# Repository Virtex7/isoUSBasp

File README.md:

isoUSBasp
=========

3kV isolated USBasp-compatible Atmel AVR8 USB programmer

description in German Language:

3kV Dauerlast-isolierter USBasp mit Leistungstreibern am Ausgang

diese Version des bekannten Atmel-Programmiergeräts USBasp von Thomas Fischl
enthält ein paar zusätzliche Fähigkeiten:

- überall LEDs
- LEDs statt Zenerdioden am USB-Port (schöner!)
- galvanisch isolierter ISP-Port
- galvanisch getrennte Target-Supplyfunktion bis 200mA in 3,3 und 5V
- automatische Einstellung der Programmierspannung
- Leistungstreiber an den Programmierpins mit je +-70mA dauerkurzschlussfest
- Schmitt-Trigger-Eingänge mit Signalrückgewinnung
- per Schalter einstellbare slowSCK-Funktionalität für 128kHz-Targets

effektiv soll dieser Programmieradapter überall eingesetzt werden, auch wenn das Target
auf einer viel höheren Spannungsebene liegt, als der zur Programmierung eingesetzte PC.
Auch werden durch eine Massetrennung Masseschleifen und damit bedingte Fehlerströme
vermieden, die zur Beschädigung des PCs und des Programmiergeräts führen können.

Desweiteren ist jeder Programmierpin mit Schutzbeschaltung gegen Überspannung,
Dauerkurzschluss und in Grenzen gegen Rückspeisung geschützt.

Die Programmierspannung stellt sich automatisch ein, wenn am Vref-Pin des ISP-Anschlusses
eine Spannung anliegt. Default ist 3,3V, auch wenn keine Spannung am Vref-Pin liegt.
Umschaltgrenze ist 3,6V, dabei wird dann auf 5V ISP-Spannung umgeschaltet.

Es ist auch möglich den Vref-Anschluss zu bestromen, also das Target mit Strom zu
versorgen. Maximalstrom ist dabei 200mA bei 5V und ca 300mA bei 3,3V, durch einen
Widerstand dauerhaft kurzschlussfest. (dabei bricht die Spannung zusammen)

Hardware:

Schaltplan und Layout und alle nötigen Libs wurden entweder von mir erstellt oder sind
Teil des OpenSource-Projekts KiCad (EDA)
Ich empfehle die Verwendung einer selbst kompilierten Version von KiCad, da diese die
aktuellste Version ist und KiCad momentan recht schnell entwickelt wird.

Software:

Das Produkt ist zu fast 100% kompatibel zur FISCHL-USBasp-Software, dafür wurden ein paar
Inverter extra verbaut, das hätte man auch in Software machen können.
Allerdings muss das Relais an PC3 nach erfolgter Anmeldung am USB angeschaltet werden,
das ist und wird die einzige Modifikation an der Software.

Daher verweise ich auch auf die Homepage von Thomas Fischl:
http://www.fischl.de/usbasp/

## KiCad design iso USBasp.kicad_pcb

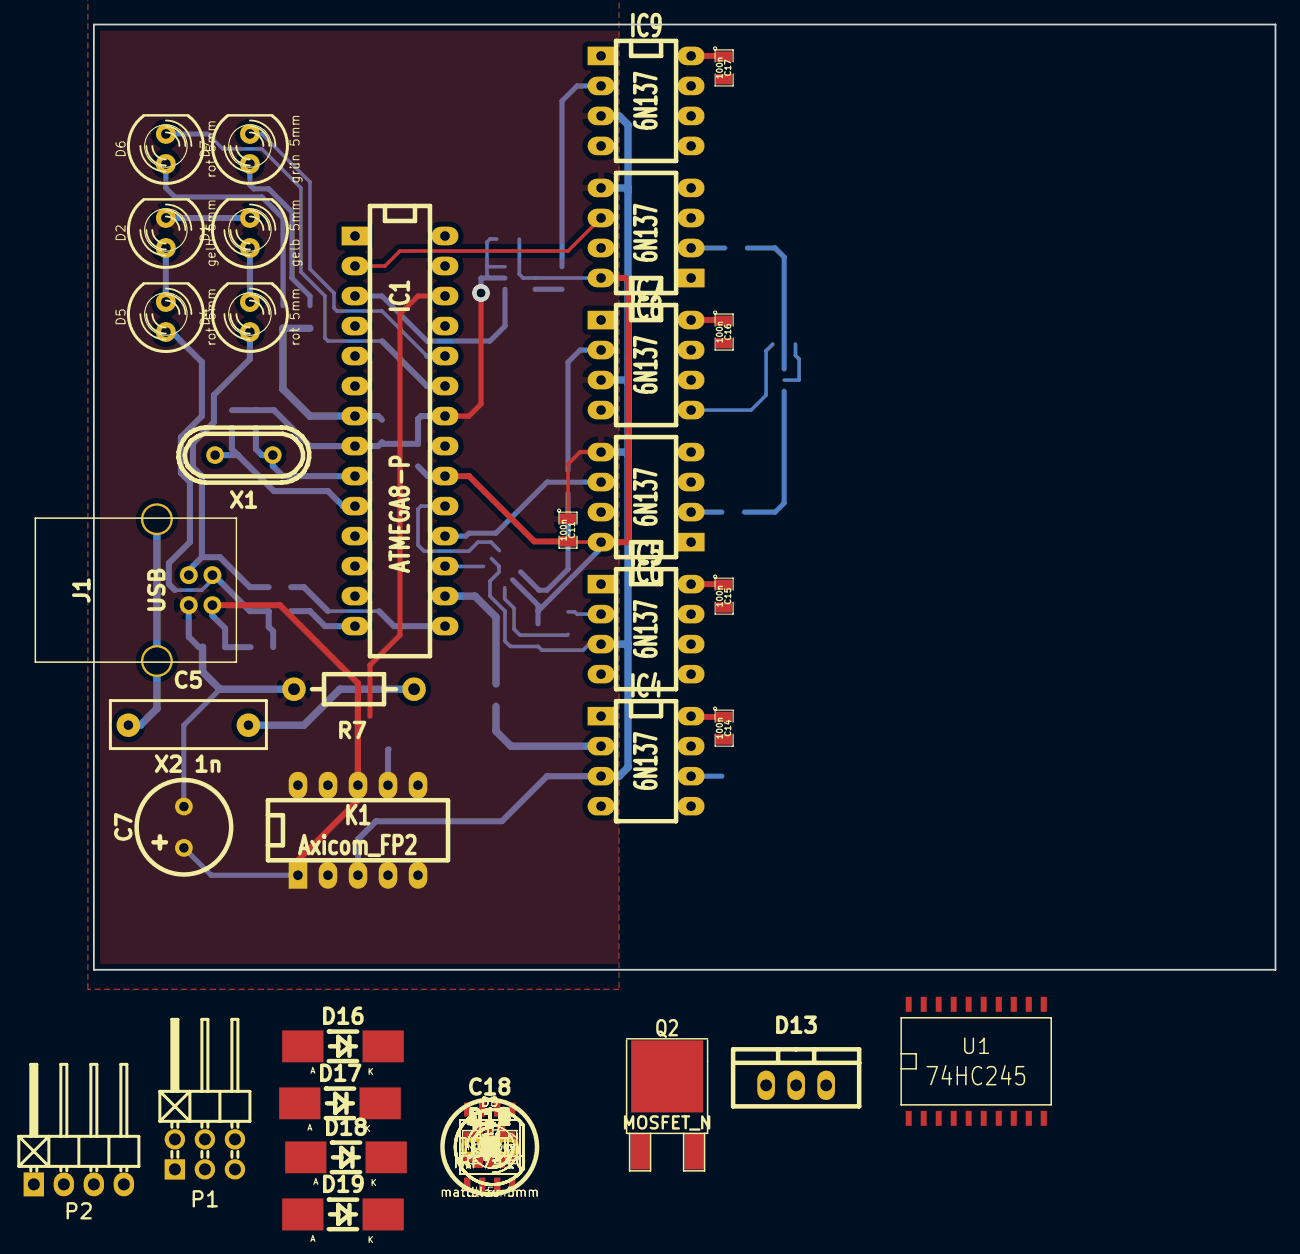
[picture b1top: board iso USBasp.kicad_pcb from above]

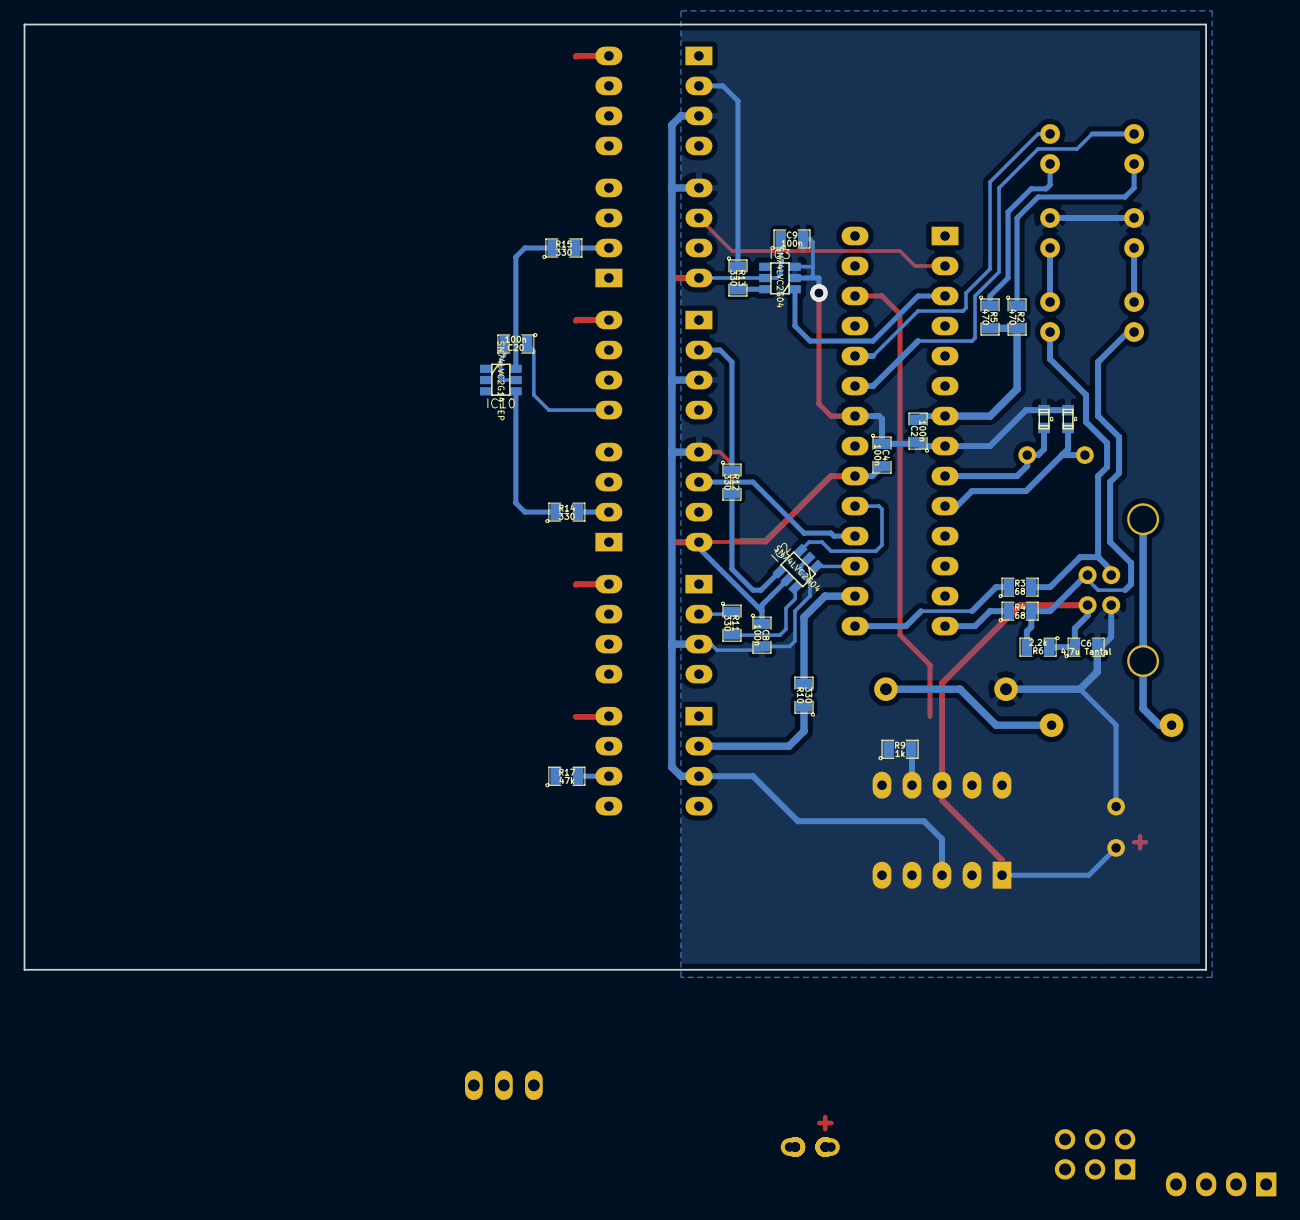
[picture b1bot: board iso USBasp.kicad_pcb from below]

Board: 2 copper layers, 100.0 x 80.0 mm, 95 parts (24 on the bottom side), 62 nets.

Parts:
C1, C3: 22p; c_0603
C2, C4, C8, C9, C10, C11, C12, C13, C14, C15, C16, C17, C20, C21, C22, C23, C24: 100n; SM0805
C5: X2 1n; Capacitor13x4RM10
C6: 4,7u Tantal; SM0805
C7, C18: 100u; Elko_vert_DM8_RM3-5
C19, C25: 10u; SM0805
D1, D2: gelb 5mm; LED-5MM
D3, D4, D5, D6: rot 5mm; LED-5MM
D7: grün 5mm; LED-5MM
D8, D9: mattblau 5mm; LED-5MM
D10: 3,6V; Diode-MiniMELF_Standard
D11, D12, D14: 5,1V; Diode-MiniMELF_Standard
D13: com. kath.; TO-220_Neutral123_Vertical
D15: 1n4148; Diode-MiniMELF_Standard
D16: 30V 1A; Diode-MELF_Handsoldering
D17, D18, D19: P6KE6,8A; Diode-MELF_Handsoldering
IC1: ATMEGA8-P; DIP-28__300_ELL
IC2, IC3: SN74LVC2G04; SOT23_6
IC4, IC5, IC6, IC7, IC8, IC9: 6N137; DIP-8__300_ELL
IC10: SN74LVC2G14-EP; SOT23_6
IC11: MCP16301; SOT23_6
IC12: TLV3501; SOT23_6
J1: USB; USB_B
K1: Axicom_FP2; DIP-10__300_ELL
L2: 15uH; SM1210
P1: CONN_3X2; Pin_Header_Angled_2x03
P2: CONN_4; Pin_Header_Angled_1x04
Q2: MOSFET_N; DPAKGDS
Q5, Q7: IRF7410; SO8N
R1, R2, R5: 470; SM0805
R3, R4: 68; SM0805
R6: 2,2k; SM0805
R7: 1M THT; Resistor_Horizontal_RM10mm
R8, R9, R18, R24, R27: 1k; SM0805
R10, R11, R12, R13, R14, R15: 330; SM0805
R16, R19: 10; SM0805
R17, R21, R23, R25, R26: 47k; SM0805
R20: 1M; SM0805
R22, R29: 10k; SM0805
R28: 31,2k; SM0805
U1: 74HC245; SO20L
X1: 12MHz; Crystal_HC49-U_Vertical

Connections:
+3.3V: C24.1, C25.1, D15.1, L2.1, R28.1
+5V: C13.1, C14.1, C15.1, C16.1, C17.1, C18.1, C19.1, C23.2, IC4.8, IC5.8, IC7.8, IC9.8, IC11.4, IC12.4, R18.2, R22.1, R24.2, R27.1
/DCDC_on: IC1.26, R8.1
/ISP_MISO: IC1.18, IC6.6
/ISP_MOSI: IC1.17, IC2.1
/ISP_RESET: IC1.16, R10.2
/ISP_SCK: IC1.19, IC2.3
/RX: IC1.2, IC8.6, P2.2, R26.1
/TX: D19.2, IC1.3, IC3.1, P2.3, U1.11, U1.12
/miso: P1.1, R25.1
/mosi: D18.2, P1.4, U1.13, U1.14, U1.15
/reset: P1.5, R16.1
/sck: D17.2, P1.3, U1.16, U1.17, U1.18
/slowSCK: D3.2, IC1.25
/targ_vcc: P1.2, P2.1, R19.1, R20.1, R21.2
AGND: C1.2, C2.1, C3.2, C4.1, C6.2, C7.2, C8.2, C9.2, C10.1, C11.1, C13.2, C14.2, C15.2, C16.2, C17.2, C18.2, C19.2, C20.1, C22.2, C23.1, C24.2, C25.2, D1.2, D2.2, D9.2, D10.1, D11.1, D12.1, D14.1, D16.1, D17.1, D18.1, D19.1, IC1.8, IC1.22, IC2.2, IC3.2, IC3.3, IC4.3, IC4.5, IC5.3, IC5.5, IC6.3, IC6.5, IC7.3, IC7.5, IC8.3, IC8.5, IC9.3, IC9.5, IC10.2, IC11.2, IC12.2, IC12.6, J1.4, K1.3, P1.6, P2.4, Q2.S, R7.2, R17.1, R20.2, R29.2, U1.10
unnamed: C1.1, IC1.10, X1.2
unnamed: C3.1, IC1.9, X1.1
unnamed: C5.1, J1.5, J1.6
unnamed: C5.2, R7.1
unnamed: C12.1, D8.2, K1.4
unnamed: C12.2, K1.7, R9.2
unnamed: C21.1, D15.2, IC11.1
unnamed: C21.2, D16.2, IC11.5, L2.2
unnamed: D1.1, D4.2
unnamed: D2.1, D5.2
unnamed: D3.1, R1.2
unnamed: D4.1, J1.3, R3.2
unnamed: D5.1, J1.2, R4.2, R6.2
unnamed: D6.1, R2.1
unnamed: D6.2, IC1.23
unnamed: D7.1, R5.1
unnamed: D7.2, IC1.24
unnamed: D8.1, R9.1
unnamed: D9.1, R18.1
unnamed: D10.2, IC12.1, R22.2
unnamed: D11.2, IC12.3, R21.1
unnamed: D12.2, IC10.1, R25.2
unnamed: D13.2, R24.1
unnamed: D13.3, R27.2
unnamed: D14.2, IC10.3, R26.2
unnamed: IC1.14, R4.1
unnamed: IC1.4, IC1.15, R3.1
unnamed: IC2.4, R12.2
unnamed: IC2.6, R11.2
unnamed: IC3.6, R13.2
unnamed: IC4.2, R10.1
unnamed: IC4.6, Q2.G, R17.2
unnamed: IC5.2, R11.1
unnamed: IC5.6, U1.5, U1.6, U1.7
unnamed: IC6.2, R14.2
unnamed: IC7.2, R12.1
unnamed: IC7.6, U1.2, U1.3, U1.4
unnamed: IC8.2, R15.2
unnamed: IC9.2, R13.1
unnamed: IC9.6, U1.8, U1.9
unnamed: IC10.4, R14.1
unnamed: IC10.6, R15.1
unnamed: IC11.3, R28.2, R29.1
unnamed: Q2.D, R16.2
unnamed: R23.1, U1.19
VCOM: C2.2, C4.2, C6.1, C7.1, C8.1, C9.1, C10.2, C11.2, C20.2, C22.1, IC1.7, IC1.20, IC2.5, IC3.5, IC6.8, IC8.8, IC10.5, J1.1, K1.1, K1.8, R1.1, R2.2, R5.2, R6.1, R23.2, U1.1, U1.20

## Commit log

2014-03-09 Update .gitignore
    change to an KiCad-Compatible Version...
2014-03-09 Update README.md
    real initial commit
2014-03-09 Schaltplan-Projekt, Plan ist an sich fertig, ggf noch Fehlerkorrekturen nötig und die zwei mosfet-Typen müssen noch spezifiziert werden.
2014-03-09 Zusatzinfo zur Software.
2014-03-09 zuordunugsdateien schaltplan -> footprints dazu, aber noch nicht fertig. + noch ein paar Änderungen am Schaltplan
2014-04-05 neue Footprints für MOSFETs und Schalter dazugefügt.
2014-04-18 Anfang des Layouts, der USB-verbundene Teil ist schon fast fertig. es fehlen noch die Footprints von Schaltern und dem TRACO-DCDC-Wandler
